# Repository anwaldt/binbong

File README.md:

# BinBong technical repository

## Overview

BingBong is a controller interface for the GLOOO Digital Music Instrument (DMI).
This repository contains all the necessary files to develop the firmaware for the controller and the receiving software patch for Pure Data.

## Requirements

### [Arduino IDE](https://www.arduino.cc/en/Main/Software)
  
- **Install through board manager**
  - [Redbear DUO Board package](https://github.com/redbear/Duo/blob/master/docs/arduino_board_package_installation_guide.md) 
    - **Important!** select version **0.3.1** when installing!

- **Install through library manager**
  -  Adafruit BNO055 library **1.1.9**
  -  Adafruit unified sensor library **1.0.3**
  -  Adafruit ADS1015 AD conversion library **1.0.0**
  -  AgileWare CircularBuffer **1.3.1**

- **Install manually**
  - Particle_osc (included in repo)
    - `cp /Arduino Libraries/particle_osc ${YOUR_ARDUINO_HOME}/libraries`

### [Pure Data (vanilla)](https://puredata.info/downloads)
  
- **Install through package manager inside PD** 
  - MrPeach

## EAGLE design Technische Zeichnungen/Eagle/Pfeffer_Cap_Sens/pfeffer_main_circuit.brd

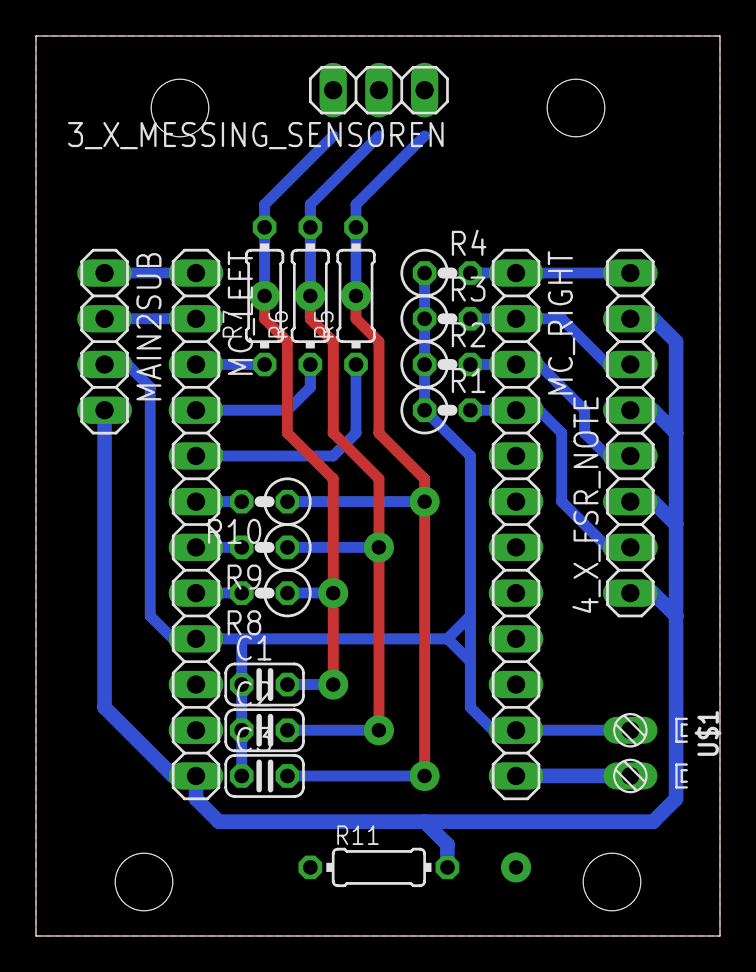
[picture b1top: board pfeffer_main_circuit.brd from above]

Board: 2 copper layers, 38.0 x 50.0 mm, 20 parts (0 on the bottom side), 18 nets.

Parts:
3_X_MESSING_SENSOREN: 1X03
4_X_FSR_NOTE: 1X08
C1, C2, C3: 10p; C025-024X044
MAIN2SUB: 1X04
MC_LEFT: 1X12
MC_RIGHT: 1X12
R1, R2, R3, R4: 10k; 0207/2V
R5, R6, R7, R11: 100k; 0204/7
R8, R9, R10: 1k; 0207/2V
U$1: DS308-02; DS308-2.54-02P

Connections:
GND: C1.1, C2.1, C3.1, MAIN2SUB.3, MC_LEFT.9, MC_RIGHT.11, R1.1, R2.1, R3.1, R4.1, R11.1, U$1.1
unnamed: 4_X_FSR_NOTE.2, MC_RIGHT.4, R1.2
unnamed: 4_X_FSR_NOTE.4, MC_RIGHT.3, R2.2
unnamed: 4_X_FSR_NOTE.6, MC_RIGHT.2, R3.2
unnamed: 4_X_FSR_NOTE.8, MC_RIGHT.1, R4.2
unnamed: MC_RIGHT.12, U$1.2
unnamed: MAIN2SUB.1, MC_LEFT.1
unnamed: MC_LEFT.6, R10.2
unnamed: 3_X_MESSING_SENSOREN.1, C3.2, R5.2, R10.1
unnamed: 3_X_MESSING_SENSOREN.2, C2.2, R6.2, R9.1
unnamed: 3_X_MESSING_SENSOREN.3, C1.2, R7.2, R8.1
unnamed: MC_LEFT.5, R5.1
unnamed: MC_LEFT.3, R7.1
unnamed: MC_LEFT.4, R6.1
unnamed: MC_LEFT.7, R9.2
unnamed: MC_LEFT.8, R8.2
unnamed: MAIN2SUB.2, MC_LEFT.2
VCC: 4_X_FSR_NOTE.1, 4_X_FSR_NOTE.3, 4_X_FSR_NOTE.5, 4_X_FSR_NOTE.7, MAIN2SUB.4, MC_LEFT.12, R11.2

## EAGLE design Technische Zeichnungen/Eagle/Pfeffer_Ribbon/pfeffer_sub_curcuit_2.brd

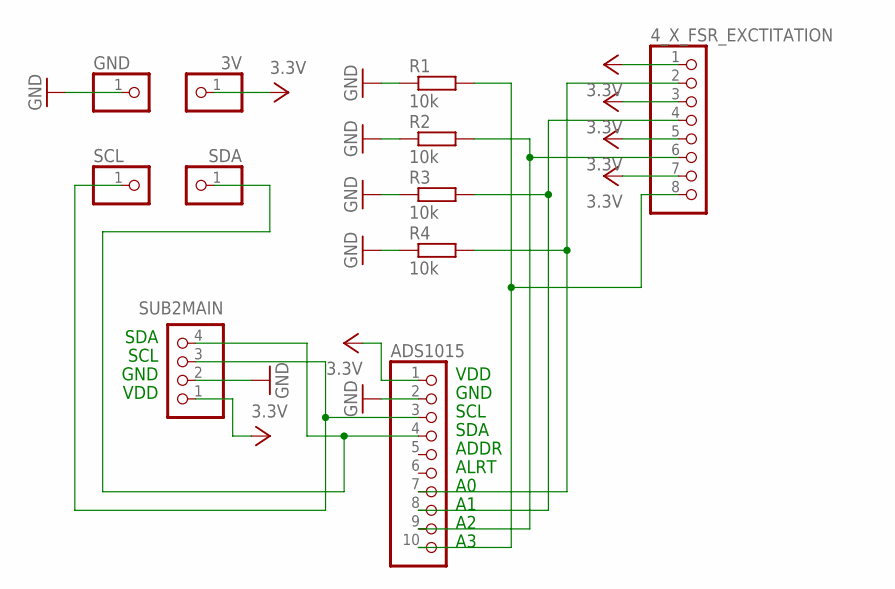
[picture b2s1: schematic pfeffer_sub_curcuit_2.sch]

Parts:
3V: PINHD-1X1; 1X01
4_X_FSR_EXCTITATION: PINHD-1X8; 1X08
ADS1015: PINHD-1X10; 1X10
GND: PINHD-1X1; 1X01
R1, R2, R3, R4: 10k; 0204/7
SCL: PINHD-1X1; 1X01
SDA: PINHD-1X1; 1X01
SUB2MAIN: PINHD-1X4; 1X04

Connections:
GND: ADS1015.2, GND.1, R1.1, R2.1, R3.1, R4.1, SUB2MAIN.2
unnamed: 4_X_FSR_EXCTITATION.8, ADS1015.10, R1.2
unnamed: 4_X_FSR_EXCTITATION.6, ADS1015.9, R2.2
unnamed: ADS1015.3, SCL.1, SUB2MAIN.3
unnamed: ADS1015.4, SDA.1, SUB2MAIN.4
unnamed: 4_X_FSR_EXCTITATION.4, ADS1015.8, R3.2
unnamed: 4_X_FSR_EXCTITATION.2, ADS1015.7, R4.2
VCC: 3V.1, 4_X_FSR_EXCTITATION.1, 4_X_FSR_EXCTITATION.3, 4_X_FSR_EXCTITATION.5, 4_X_FSR_EXCTITATION.7, ADS1015.1, SUB2MAIN.1

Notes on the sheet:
VDD
GND
SCL
SDA
ADDR
ALRT

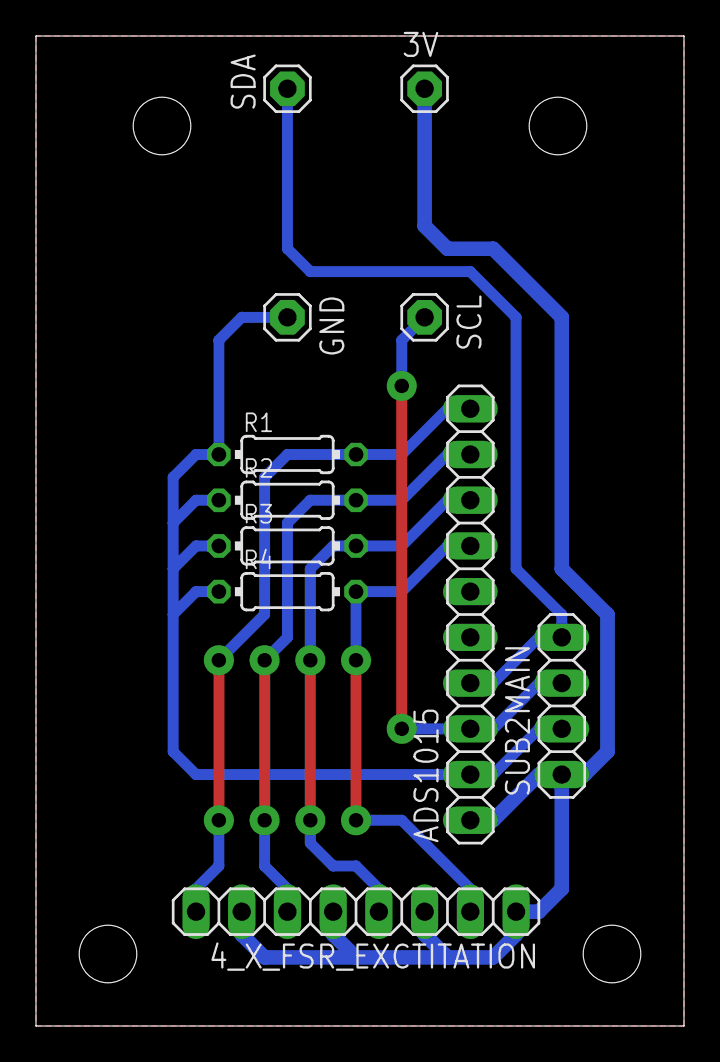
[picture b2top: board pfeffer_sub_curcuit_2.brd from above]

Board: 2 copper layers, 36.0 x 55.0 mm, 11 parts (0 on the bottom side), 8 nets.

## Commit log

2018-02-26 added techn. drawing and firmware
2018-02-28 added pcb layouts (eagle)
2018-02-28 added layout rules to both egale projects
2018-02-28 added Specs
2018-02-28 updated ribbon pcb layout
2018-02-28 added usefull links
2018-02-28 no the links should work...
2018-02-28 added PureData Receiver Patch
2018-03-05 updated PCBs and the technical Drawing
2018-03-05 added 3D Lab Link
2018-04-18 added ribbon testing, firmware and applied it to the new firmware, added a new tech. drawing, added new PCB layouts
2018-04-18 added BinBong Partslist
2018-05-23 little but significant changes to the schemtaics and circuit
2018-05-23 added particle_osc lib
2018-05-23 added further Arduino Libraries
2018-09-18 Changed to manual IP for OSC receiver!
2018-10-11 Merging BinBong into GLOO synth!
2018-10-19 Adding PD receiver module!
2018-10-19 Started debugging all BinBongs!
2018-10-19 Added individual OSC-path for IP xxx:xxx:xxx:102!
2018-11-04 Sending two bundles (FSR,IMU) - PD patch showing all sensors! (but temperature ...)
2018-11-06 Routine commit!
2018-11-07 First tests with bong and synth, using PD as OSC perser - kind of working!
2018-11-08 Added calibration for the FSRs at startup! (by subtracting the pressure when unpressed)
2018-11-08 Starting a doc!
2018-11-29 Decreased valve threshold to 150!
2019-01-13 Improved dynamic creation!
2019-01-13 Disabled serial port!
2019-01-13 Improved scaling for valve sensors!
2019-01-13 Improved PAD-fsr scaling!
2019-01-22 Sensor fusion now in main patch!
2019-01-22 Outsourced the absolute orientation to function - UNTESTED!
2019-07-02 Switched to WiFi connection to Notlandung!
2019-10-02 firmware: Modular structure.
    Refactoring to modular structure to make further modifications simpler.
2019-10-02 firmware: New version supporting the new IMU.
    Add support for the BN055 sensor fusion package.
    Provide pitch, roll and heading to OSC.
2019-10-02 puredata: Updated scaling.
2019-10-02 Working with new BinBong!
2019-10-02 firmware: Working version with BNO055 and new power circuit.
    Refactor display functions. Send calibration status data to puredata.
2019-10-02 puredata: minor update to received IMU values
    change scaling of values according to the ones provided by BN055
2019-10-02 firmware: changed valve sensor processing from bitmask to integer mode
2019-10-02 firmware: quick fix.
    Change to correct wifi network. Add forgotten pad function, was not
    working.
2019-10-02 remote: added various mapping features and controls
2019-10-02 firmware: hanged receiver ip to *.200
2019-10-02 Added BINBONG credentials!
2019-10-02 remote: after SIM demo
2019-10-02 remote: added tonal/noise control
2019-10-02 firmware: sending note values without octave shifting
2019-10-02 firmware: Remove old versions and redundant test files.
    Small cleanup before merging new_imu version to master.
2019-10-16 firmware: Updated ip address of the gateway.
    Changed ip address due to firmware update on the gateway.
    Minor cleanup of various print messages.
2019-10-16 puredata: added package counter.
    Added counter for bundles/second for debugging purposes.
2019-11-06 firmware: Revert credentials, add documentation.
    Reverted to using the fritzbox due to reliability issues with the
    tp-link device.
    Added documentation on how to do fres install of the development environment.
2019-11-06 documentation: quick fix for list
2019-11-20 firmware: Enable swipe gesture for octave change.
    Collect finger position delta values in a buffer and sum them to detect
    swiping gestures.
    This is much more convenient than the old way of having static mapping
    of the ribbon as octave zones. Old position information is not
    conflicting and can be used for some other mapping if needed.
2019-11-20 firmware: Delete vendored libraries.
    Remove static libraries as they can all installed much easier from
    arduino library manager and this ensures that the compiler finds them
    by default if the user is using arduino IDE.
2019-12-04 New mapping sketch
2019-12-07 pd: added sends for all bong parameters (only in PureData/BINBONG_receiver_new_imu.pd)!
2019-12-22 PD: added send for full OSC package from bong.
2019-12-22 Cleanup of receiver
2020-01-04 PD: latest version with 0..1 mappings
2020-04-10 Merging all branches in GLOOO!
2021-02-02 Moving!
